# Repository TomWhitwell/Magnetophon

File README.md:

# Magnetophon  

With a mono cassette head in the panel and a NAB equalised ampli er circuit, Magnetophon is a cassette player without the transport mechanism. Try rubbing old cassette tapes on the panel, or attach a head on a wire to recreate Nam June Paik’s
Random Access or Laurie Anderson's Tape Bow Violin. 

[Schematic](https://github.com/TomWhitwell/Magnetophon/blob/master/Collateral/Magnetophon_schematic.pdf)

[Magnetophon is in this video from SuperBooth16 in Berlin](https://youtu.be/UVMrQejVZlw?t=4m26s) 

[Magnetophon vs Nagra audio torture test. The Nagra sounds better(!) but it gets fun when the Magnetophon head starts moving](https://soundcloud.com/musicthing/nagra-v-magnetophon)

BOM: 

- 2 x Thonkiconn Sockets 
- 1 x 50k Alpha Potentiometer (from Thonk, with bushing)  
- 1 x 10 pin 5x2 Euro power header 
- 1 x TL072 op amp 
- 1 x CTH1M MONO cassette playback head
- 2 x Poly Fuses (100ma blow or higher) 
- 2 x 1N4001 diodes 
- 1 x 47uf Electrolytic Capacitor* 
- 2 x 10uf Electrolytic Capacitors* 
- 2 x 100nf Ceramic Capacitor 
- 1 x 15nf Polybox Capacitor
- 1 x 200k resistor 
- 1 x 3.6k resistor 
- 1 x 2.2k resistor 
- 1 x 470R resistor 
- 2 x 200R resistor 
- Notes: 
- C7 is NOT required but a space is left on the board in case you have any oscillation in the first op amp stage. 
- *Electo caps should be short - 7mm tall - to fit between the boards. Otherwise, you can mount them on the back if you are careful of polarity. 

Status: 
- May 2016: Rev 1 (= Proto 2 with silkscreen tweaks) should be good to build. 
- Proto 2 works well. 
- Proto 2 designed and sent to fab 
- Proto 1 used for 4 days straight at SuperBooth 
- Proto 1 built, needed extra capactitor to kill huge ultrasonic oscillation
- Not verified 
- January 2016 Prototype sent for manufacture 
- October 2015 Designed 

Named after the [AEG Magnetophon](http://www.aes.org/aeshc/docs/recording.technology.history/tape.html), the first commercial tape recorder, revealed at the 1935 Radio Fair in Berlin. 

([Image via AES](http://www.aes.org/aeshc/docs/recording.technology.history/tape.html))

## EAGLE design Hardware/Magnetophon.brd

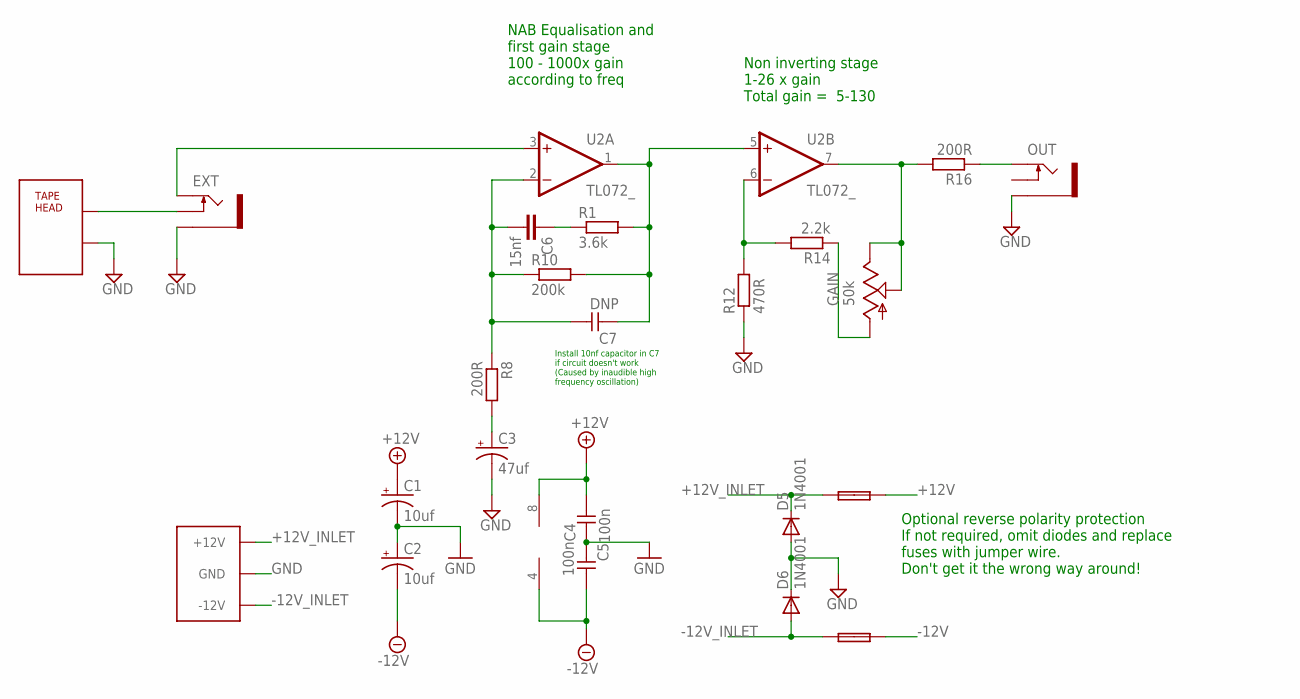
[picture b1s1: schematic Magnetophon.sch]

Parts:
1: FUSE; C050H075X075
C1, C2: 10uf; CPOL-RADIAL-10UF-25V
C3: 47uf; CPOL-RADIAL-10UF-25V
C4, C5: 100n; C050-024X044
C6: 15nf; C050-030X075
C7: DNP; C050-024X044
D5, D6: 1N4001; DO41-10
EXT: THONKICONNNEW; WQP-PJ301M-12_JACK
FUSE: FUSE; C050H075X075
GAIN: 50k; EVUF
OUT: THONKICONNNEW; WQP-PJ301M-12_JACK
R1: 3.6k; 7MM_RESISTOR
R8, R16: 200R; 7MM_RESISTOR
R10: 200k; 7MM_RESISTOR
R12: 470R; 7MM_RESISTOR
R14: 2.2k; 7MM_RESISTOR
U2: TL072_; DIL08
U$1: MONO_CASSETTE_HEAD
U$2: EURO_POWER_LOCK; EURO_PWR_HEADER_LOCK

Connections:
+12V: 1.2, C1.1 (+), C4.1, U2.8 (V+)
+12V_INLET: 1.1, D5.C, U$2.POS1 (+12V), U$2.POS2 (+12V)
-12V: C2.2 (-), C5.1, FUSE.2, U2.4 (V-)
-12V_INLET: D6.A, FUSE.1, U$2.NEG1 (-12V), U$2.NEG2 (-12V)
FROMHEAD: EXT.P$2_SWITCH (SWITCH), U$1.P$1
GND: C1.2 (-), C2.1 (+), C3.2 (-), C4.2, C5.2, D5.A, D6.C, EXT.P$3_SLEEVE (SLEEVE), OUT.P$3_SLEEVE (SLEEVE), R12.1, U$1.P$2, U$2.GND1 (GND), U$2.GND2 (GND), U$2.GND3 (GND), U$2.GND4 (GND), U$2.GND5 (GND), U$2.GND6 (GND)
unnamed: C6.2, C7.1, R8.1, R10.1, U2.2 (-IN)
unnamed: C7.2, R1.2, R10.2, U2.1 (OUT), U2.5 (+IN)
unnamed: GAIN.1 (A), R14.1
unnamed: R12.2, R14.2, U2.6 (-IN)
unnamed: C3.1 (+), R8.2
unnamed: GAIN.2 (S), GAIN.3 (E), R16.2, U2.7 (OUT)
unnamed: C6.1, R1.1
unnamed: OUT.P$1_TIP (TIP), R16.1
TOAMP: EXT.P$1_TIP (TIP), U2.3 (+IN)

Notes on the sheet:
NAB Equalisation and first gain stage 100 - 1000x gain according to freq
Non inverting stage 1-26 x gain Total gain = 5-130
Optional reverse polarity protection If not required, omit diodes and replace fuses with jumper wire. Don't get it the wrong way around!
Install 10nf capacitor in C7 if circuit doesn't work (Caused by inaudible high frequency oscillation)

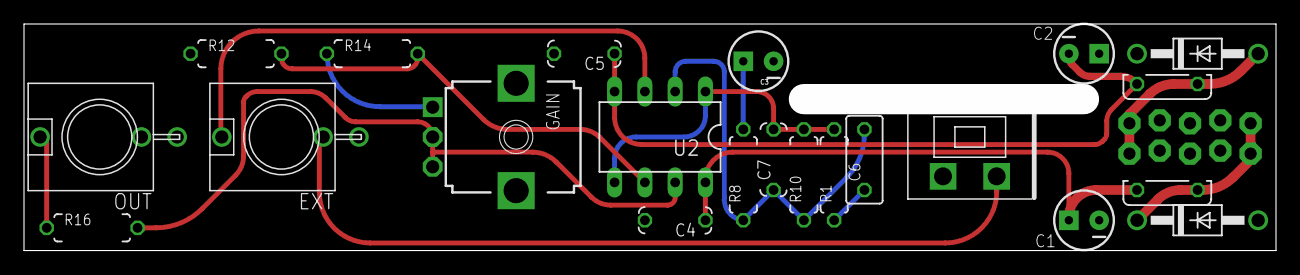
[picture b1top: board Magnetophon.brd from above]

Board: 4 copper layers, 105.0 x 19.0 mm, 23 parts (1 on the bottom side), 15 nets.

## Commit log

2015-10-07 First upload
2015-10-08 double!
2015-10-08 Starting layout
2015-10-11 First pcb layout
2015-10-12 Start panel
2015-10-16 panel design
2015-10-17 panel finished
2015-10-17 Design complete - to do: Checking hole size for playback head
2015-10-18 Tweaks
2015-10-18 filename changes
2016-01-25 Add via to ground panel artwork
2016-01-25 img upload
2016-01-26 Prototype 1 finalised design and gerbers
2016-01-26 cleanup
2016-04-07 add 10n cap and reroute
2016-04-09 improved layout and curves
2016-04-09 Prototype 2 Gerbers
2016-04-09 pics
2016-05-03 Small board tweaks, fixes #1, fixes #2, fixes #3, fixes #4
    #1 and #2 fixed by improved layout, #3 and #4 with tweaks here
2016-05-05 Rev 1 Gerbers
2016-06-04 upload schematic
2016-08-04 Fix issue with trace crossing cutout
2016-08-20 update details
2016-08-20 Revised Panel, renamed as MAGNETOPHON
2016-08-20 Slightly revised Panel + new image
2016-08-20 Tidy up
2016-08-22 Update panel eagle file to remove old logo
2016-09-08 Update board design
2016-09-08 gitignore
2016-09-08 Version 1.1 Gerbers, fix cutout/trace issue
2016-10-28 update R12 to improve gain
2016-10-28 Schematic image
2016-10-28 Reroute to avoid space under socket
2017-02-27 1.2 version, removed old Gerber files

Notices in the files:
Hardware/Magnetophon.brd:
PCB Rev 1.2 CC-BY-SA
parts and their libraries:
SparkFun-Passives: Licensing: CC v3.0 Share-Alike You are welcome to use this library for commercial purposes.
